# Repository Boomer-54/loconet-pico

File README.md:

# LocoNet-Pico Servoboard

LocoNet-Modul mit Raspberry Pi Pico für 16 Servos (J12–J27).
KiCad-Projekt, Schaltplan als PDF und Fertigungsdaten liegen in [`loconet-pico/`](loconet-pico/).

*Bestücktes Board im Testaufbau, noch mit der kleinen Klemme J11 (2,54 mm Raster).*

## LocoNet-Anbindung

- **Empfang:** Transistor-Eingangsstufe statt Spannungsteiler.
  R3 47k / R7 10k an Q3 (BC337) ergeben eine Schaltschwelle von ca. 3,4–4 V
  (logisch „1“ ab 4 V wird sicher erkannt),
  Q4 invertiert zurück (Leitung High = RX High), keine Invertierung in der Firmware nötig.
  Last am Bus ≥ 47 kΩ.
- **Senden:** Q1 (BC557) / Q2 (BC337) ziehen die Leitung über D1 (1N5818) auf Masse.
- **Schutz:** TVS-Diode D3 (P6KE18CA) am LocoNet, nah an J9/J10.

## Getestet mit

- Zentrale: YaMoRC YD7001
- Rocrail ab Revision 7547

## Stromversorgung

Die Servos brauchen externe 5 V über J11. USB reicht nur zum Testen mit 1–2 Servos.
GND von Pico und externer Quelle verbinden.

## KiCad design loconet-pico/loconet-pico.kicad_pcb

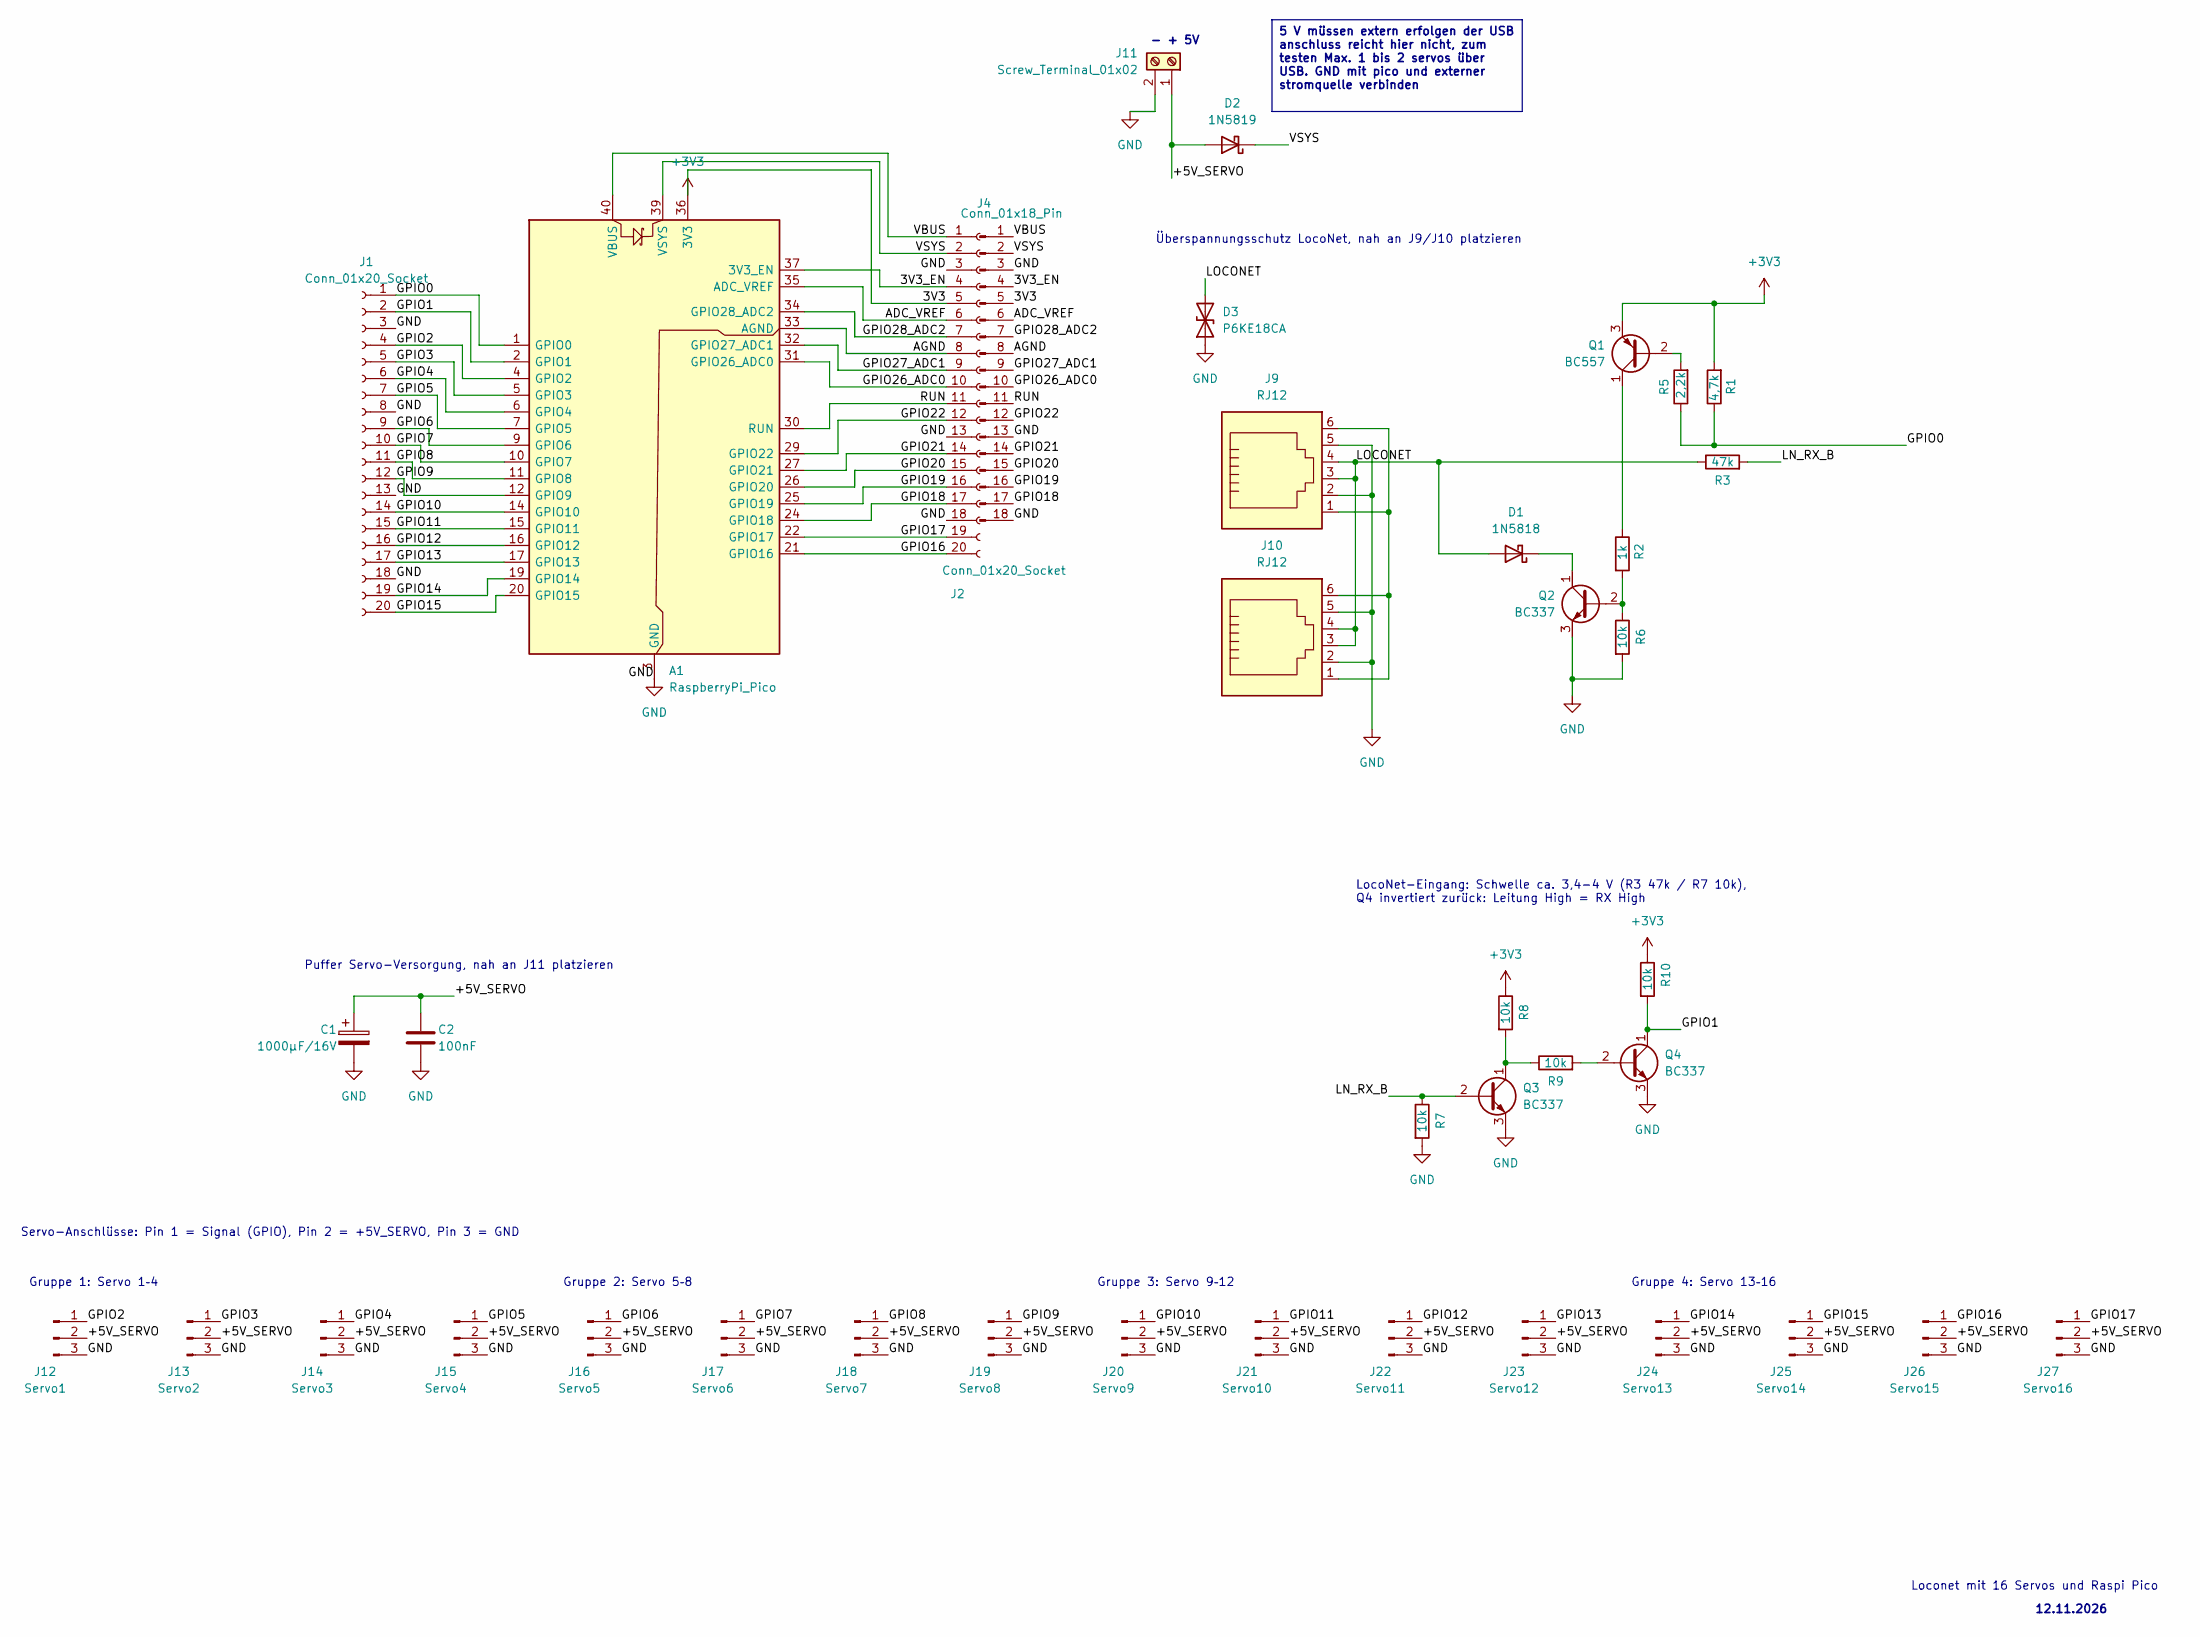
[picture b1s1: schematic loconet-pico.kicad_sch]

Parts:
A1: RaspberryPi_Pico; RaspberryPi_Pico_Common_Unspecified
C1: 1000µF/16V; CP_Radial_D10.0mm_P5.00mm
C2: 100nF; C_Disc_D5.0mm_W2.5mm_P5.00mm
D1: 1N5818; D_DO-41_SOD81_P7.62mm_Horizontal
D2: 1N5819; D_DO-41_SOD81_P10.16mm_Horizontal
D3: P6KE18CA; D_DO-15_P10.16mm_Horizontal
J1, J2: Conn_01x20_Socket; PinSocket_1x20_P2.54mm_Vertical
J4: Conn_01x18_Pin; PinHeader_1x18_P2.54mm_Vertical
J9, J10: RJ12; RJ12_Amphenol_54601-x06_Horizontal
J11: Screw_Terminal_01x02; TerminalBlock_Phoenix_MKDS-1,5-2-5.08_1x02_P5.08mm_Horizont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
J12: Servo1; PinHeader_1x03_P2.54mm_Vertical
J13: Servo2; PinHeader_1x03_P2.54mm_Vertical
J14: Servo3; PinHeader_1x03_P2.54mm_Vertical
J15: Servo4; PinHeader_1x03_P2.54mm_Vertical
J16: Servo5; PinHeader_1x03_P2.54mm_Vertical
J17: Servo6; PinHeader_1x03_P2.54mm_Vertical
J18: Servo7; PinHeader_1x03_P2.54mm_Vertical
J19: Servo8; PinHeader_1x03_P2.54mm_Vertical
J20: Servo9; PinHeader_1x03_P2.54mm_Vertical
J21: Servo10; PinHeader_1x03_P2.54mm_Vertical
J22: Servo11; PinHeader_1x03_P2.54mm_Vertical
J23: Servo12; PinHeader_1x03_P2.54mm_Vertical
J24: Servo13; PinHeader_1x03_P2.54mm_Vertical
J25: Servo14; PinHeader_1x03_P2.54mm_Vertical
J26: Servo15; PinHeader_1x03_P2.54mm_Vertical
J27: Servo16; PinHeader_1x03_P2.54mm_Vertical
Q1: BC557; TO-92
Q2, Q3, Q4: BC337; TO-92
R1: 4,7k; R_Axial_DIN0207_L6.3mm_D2.5mm_P7.62mm_Horizontal
R2: 1k; R_Axial_DIN0207_L6.3mm_D2.5mm_P7.62mm_Horizontal
R3: 47k; R_Axial_DIN0207_L6.3mm_D2.5mm_P7.62mm_Horizontal
R5: 2,2k; R_Axial_DIN0207_L6.3mm_D2.5mm_P7.62mm_Horizontal
R6, R7, R8, R9, R10: 10k; R_Axial_DIN0207_L6.3mm_D2.5mm_P7.62mm_Horizontal

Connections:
+3V3: A1.36 (3V3), J2.5, J4.5, Q1.3 (E), R1.2, R8.1, R10.1
/3V3_EN: A1.37 (3V3_EN), J2.4, J4.4
/+5V_SERVO: C1.1, C2.1, D2.2 (A), J11.1, J12.2, J13.2, J14.2, J15.2, J16.2, J17.2, J18.2, J19.2, J20.2, J21.2, J22.2, J23.2, J24.2, J25.2, J26.2, J27.2
/ADC_VREF: A1.35 (ADC_VREF), J2.6, J4.6
/AGND: A1.33 (AGND), J2.8, J4.8
/GPIO0: A1.1 (GPIO0), J1.1, R1.1, R5.1
/GPIO1: A1.2 (GPIO1), J1.2, Q4.1 (C), R10.2
/GPIO2: A1.4 (GPIO2), J1.4, J12.1
/GPIO3: A1.5 (GPIO3), J1.5, J13.1
/GPIO4: A1.6 (GPIO4), J1.6, J14.1
/GPIO5: A1.7 (GPIO5), J1.7, J15.1
/GPIO6: A1.9 (GPIO6), J1.9, J16.1
/GPIO7: A1.10 (GPIO7), J1.10, J17.1
/GPIO8: A1.11 (GPIO8), J1.11, J18.1
/GPIO9: A1.12 (GPIO9), J1.12, J19.1
/GPIO10: A1.14 (GPIO10), J1.14, J20.1
/GPIO11: A1.15 (GPIO11), J1.15, J21.1
/GPIO12: A1.16 (GPIO12), J1.16, J22.1
/GPIO13: A1.17 (GPIO13), J1.17, J23.1
/GPIO14: A1.19 (GPIO14), J1.19, J24.1
/GPIO15: A1.20 (GPIO15), J1.20, J25.1
/GPIO16: A1.21 (GPIO16), J2.20, J26.1
/GPIO17: A1.22 (GPIO17), J2.19, J27.1
/GPIO18: A1.24 (GPIO18), J2.17, J4.17
/GPIO19: A1.25 (GPIO19), J2.16, J4.16
/GPIO20: A1.26 (GPIO20), J2.15, J4.15
/GPIO21: A1.27 (GPIO21), J2.14, J4.14
/GPIO22: A1.29 (GPIO22), J2.12, J4.12
/GPIO26_ADC0: A1.31 (GPIO26_ADC0), J2.10, J4.10
/GPIO27_ADC1: A1.32 (GPIO27_ADC1), J2.9, J4.9
/GPIO28_ADC2: A1.34 (GPIO28_ADC2), J2.7, J4.7
/LN_RX_B: Q3.2 (B), R3.2, R7.1
/LOCONET: D1.2 (A), D3.2 (A2), J9.3, J9.4, J10.3, J10.4, R3.1
/RUN: A1.30 (RUN), J2.11, J4.11
/VBUS: A1.40 (VBUS), J2.1, J4.1
/VSYS: A1.39 (VSYS), D2.1 (K), J2.2, J4.2
GND: A1.3 (GND), A1.8 (GND), A1.13 (GND), A1.18 (GND), A1.23 (GND), A1.28 (GND), A1.38 (GND), C1.2, C2.2, D3.1 (A1), J1.3, J1.8, J1.13, J1.18, J2.3, J2.13, J2.18, J4.3, J4.13, J4.18, J9.2, J9.5, J10.2, J10.5, J11.2, J12.3, J13.3, J14.3, J15.3, J16.3, J17.3, J18.3, J19.3, J20.3, J21.3, J22.3, J23.3, J24.3, J25.3, J26.3, J27.3, Q2.3 (E), Q3.3 (E), Q4.3 (E), R6.2, R7.2
unnamed: D1.1 (K), Q2.1 (C)
unnamed: J9.1, J9.6, J10.1, J10.6
unnamed: Q1.2 (B), R5.2
unnamed: Q1.1 (C), R2.1
unnamed: Q2.2 (B), R2.2, R6.1
unnamed: Q3.1 (C), R8.2, R9.1
unnamed: Q4.2 (B), R9.2

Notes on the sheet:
LocoNet-Eingang: Schwelle ca. 3,4-4 V (R3 47k / R7 10k), Q4 invertiert zurück: Leitung High = RX High
Loconet mit 16 Servos und Raspi Pico
Gruppe 1: Servo 1–4
Gruppe 3: Servo 9–12
Gruppe 2: Servo 5–8
Gruppe 4: Servo 13–16
Servo-Anschlüsse: Pin 1 = Signal (GPIO), Pin 2 = +5V_SERVO, Pin 3 = GND
Überspannungsschutz LocoNet, nah an J9/J10 platzieren
Puffer Servo-Versorgung, nah an J11 platzieren
- + 5V
12.11.2026
5 V müssen extern erfolgen der USB anschluss reicht hier nicht, zum testen Max. 1 bis 2 servos über USB. GND mit pico und externer stromquelle verbinden

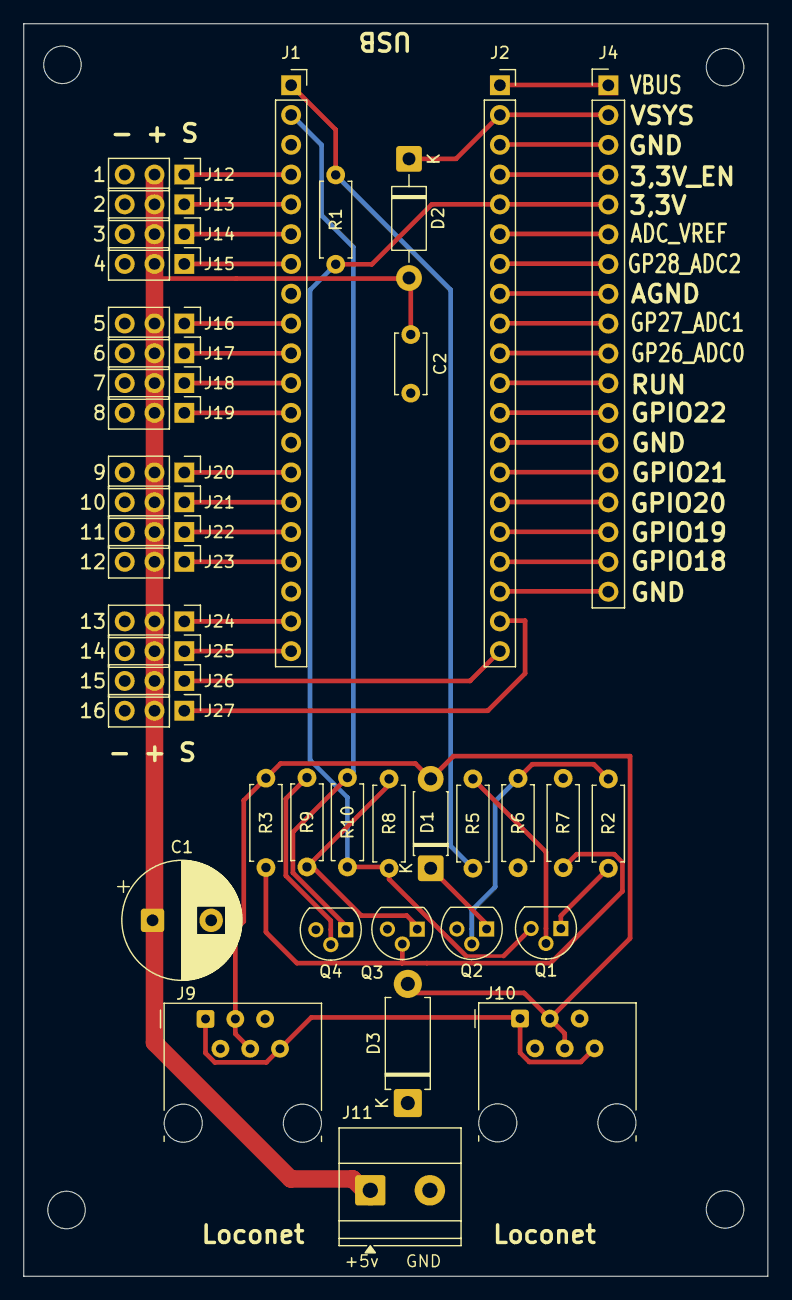
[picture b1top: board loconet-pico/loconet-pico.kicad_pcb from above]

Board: 2 copper layers, 63.4 x 106.8 mm, 44 parts (0 on the bottom side), 44 nets.

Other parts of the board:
H1, H2, H3, H4: MountingHole_3.2mm_M3

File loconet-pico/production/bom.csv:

Designator,Footprint,Quantity,Value,LCSC Part #
C1,CP_Radial_D10.0mm_P5.00mm,1,1000µF/16V,
C2,C_Disc_D5.0mm_W2.5mm_P5.00mm,1,100nF,
D1,D_DO-41_SOD81_P7.62mm_Horizontal,1,1N5818,
D2,D_DO-41_SOD81_P10.16mm_Horizontal,1,1N5819,
D3,D_DO-15_P10.16mm_Horizontal,1,P6KE18CA,
"J1, J2",PinSocket_1x20_P2.54mm_Vertical,2,Conn_01x20_Socket,
"J10, J9",RJ12_Amphenol_54601-x06_Horizontal,2,RJ12,
J11,"TerminalBlock_Phoenix_MKDS-1,5-2-5.08_1x02_P5.08mm_Horizontal",1,Screw_Terminal_01x02,
J12,PinHeader_1x03_P2.54mm_Vertical,1,Servo1,
J13,PinHeader_1x03_P2.54mm_Vertical,1,Servo2,
J14,PinHeader_1x03_P2.54mm_Vertical,1,Servo3,
J15,PinHeader_1x03_P2.54mm_Vertical,1,Servo4,
J16,PinHeader_1x03_P2.54mm_Vertical,1,Servo5,
J17,PinHeader_1x03_P2.54mm_Vertical,1,Servo6,
J18,PinHeader_1x03_P2.54mm_Vertical,1,Servo7,
J19,PinHeader_1x03_P2.54mm_Vertical,1,Servo8,
J20,PinHeader_1x03_P2.54mm_Vertical,1,Servo9,
J21,PinHeader_1x03_P2.54mm_Vertical,1,Servo10,
J22,PinHeader_1x03_P2.54mm_Vertical,1,Servo11,
J23,PinHeader_1x03_P2.54mm_Vertical,1,Servo12,
J24,PinHeader_1x03_P2.54mm_Vertical,1,Servo13,
J25,PinHeader_1x03_P2.54mm_Vertical,1,Servo14,
J26,PinHeader_1x03_P2.54mm_Vertical,1,Servo15,
J27,PinHeader_1x03_P2.54mm_Vertical,1,Servo16,
J4,PinHeader_1x18_P2.54mm_Vertical,1,Conn_01x18_Pin,
Q1,TO-92,1,BC557,
"Q2, Q3, Q4",TO-92,3,BC337,
R1,R_Axial_DIN0207_L6.3mm_D2.5mm_P7.62mm_Horizontal,1,"4,7k",
"R10, R6, R7, R8, R9",R_Axial_DIN0207_L6.3mm_D2.5mm_P7.62mm_Horizontal,5,10k,
R2,R_Axial_DIN0207_L6.3mm_D2.5mm_P7.62mm_Horizontal,1,1k,
R3,R_Axial_DIN0207_L6.3mm_D2.5mm_P7.62mm_Horizontal,1,47k,
R5,R_Axial_DIN0207_L6.3mm_D2.5mm_P7.62mm_Horizontal,1,"2,2k",

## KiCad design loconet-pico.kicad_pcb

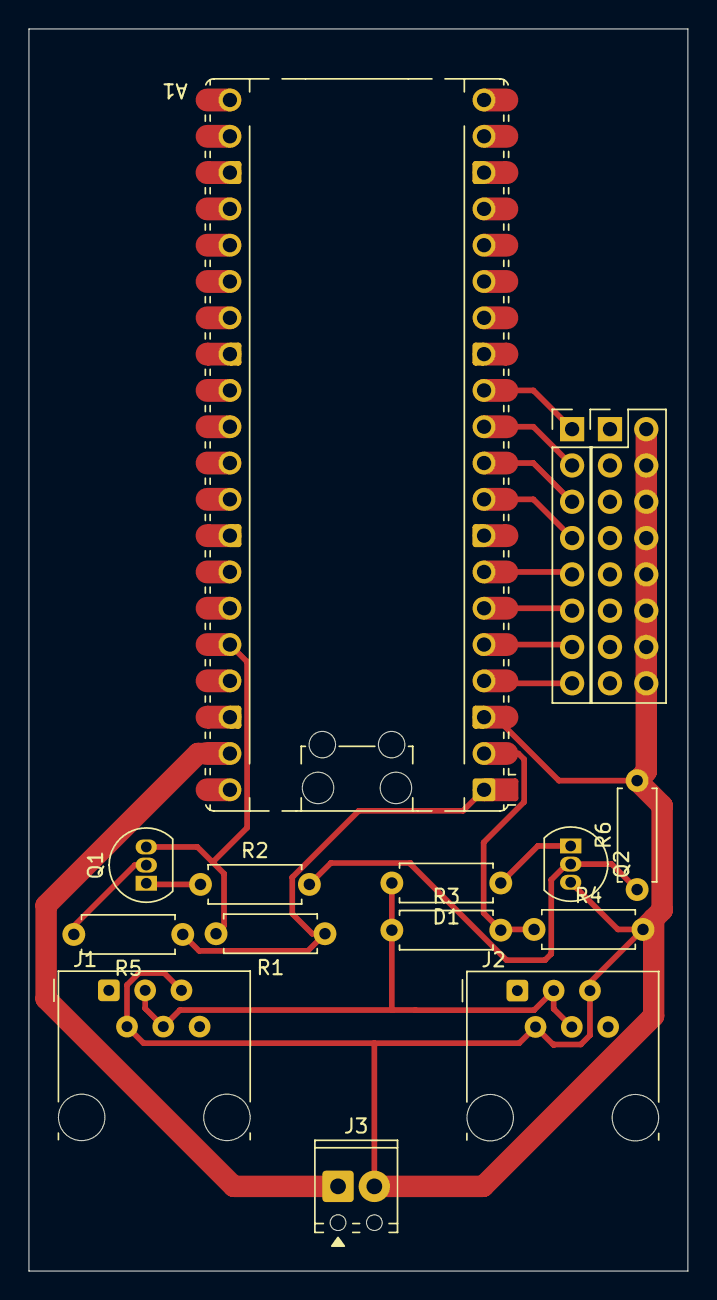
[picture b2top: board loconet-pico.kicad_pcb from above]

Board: 2 copper layers, 46.1 x 86.9 mm, 13 parts (0 on the bottom side), 10 nets.

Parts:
A1: RaspberryPi_Pico; RaspberryPi_Pico_Common_Unspecified
D1: 1N5818; R_Axial_DIN0207_L6.3mm_D2.5mm_P7.62mm_Horizontal
J1, J2: RJ12; RJ12_Amphenol_54601-x06_Horizontal
J3: Screw_Terminal_01x02; TerminalBlock_Phoenix_MPT-0,5-2-2.54_1x02_P2.54mm_Horizontal
Q1: BC557; TO-92_Inline
Q2: BC337; TO-92_Inline
R1: 4,7k; R_Axial_DIN0207_L6.3mm_D2.5mm_P7.62mm_Horizontal
R2: 1k; R_Axial_DIN0207_L6.3mm_D2.5mm_P7.62mm_Horizontal
R3, R6: 10k; R_Axial_DIN0207_L6.3mm_D2.5mm_P7.62mm_Horizontal
R4: 3,9k; R_Axial_DIN0207_L6.3mm_D2.5mm_P7.62mm_Horizontal
R5: 2,2k; R_Axial_DIN0207_L6.3mm_D2.5mm_P7.62mm_Horizontal

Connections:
+5V: A1.39 (VSYS), J3.1
/RX: A1.2 (GPIO1), R3.2, R4.1
/TX: A1.1 (GPIO0), R1.1, R5.1
GND: A1.3 (GND), A1.8 (GND), A1.13 (GND), A1.18 (GND), A1.23 (GND), A1.28 (GND), A1.38 (GND), J1.2, J1.5, J2.2, J2.5, J3.2, Q2.3 (E), R4.2, R6.2
unnamed: A1.36 (3V3), Q1.3 (E), R1.2
unnamed: D1.2 (A), J1.3, J1.4, J2.3, J2.4, R3.1
unnamed: D1.1 (K), Q2.1 (C)
unnamed: Q1.2 (B), R5.2
unnamed: Q1.1 (C), R2.1
unnamed: Q2.2 (B), R2.2, R6.1
